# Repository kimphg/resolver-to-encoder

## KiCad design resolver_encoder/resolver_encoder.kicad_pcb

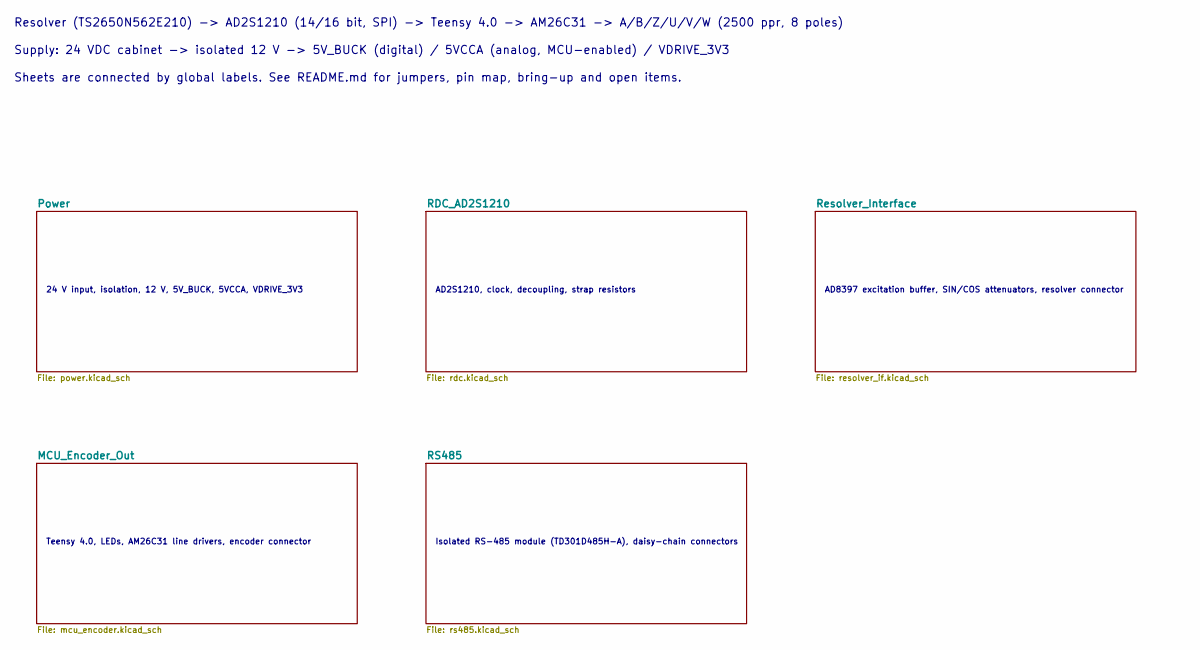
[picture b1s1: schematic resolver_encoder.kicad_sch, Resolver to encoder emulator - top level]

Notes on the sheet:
Resolver (TS2650N562E210) -> AD2S1210 (14/16 bit, SPI) -> Teensy 4.0 -> AM26C31 -> A/B/Z/U/V/W (2500 ppr, 8 poles)
Supply: 24 VDC cabinet -> isolated 12 V -> 5V_BUCK (digital) / 5VCCA (analog, MCU-enabled) / VDRIVE_3V3
Sheets are connected by global labels. See README.md for jumpers, pin map, bring-up and open items.
24 V input, isolation, 12 V, 5V_BUCK, 5VCCA, VDRIVE_3V3
AD2S1210, clock, decoupling, strap resistors
AD8397 excitation buffer, SIN/COS attenuators, resolver connector
Teensy 4.0, LEDs, AM26C31 line drivers, encoder connector
Isolated RS-485 module (TD301D485H-A), daisy-chain connectors

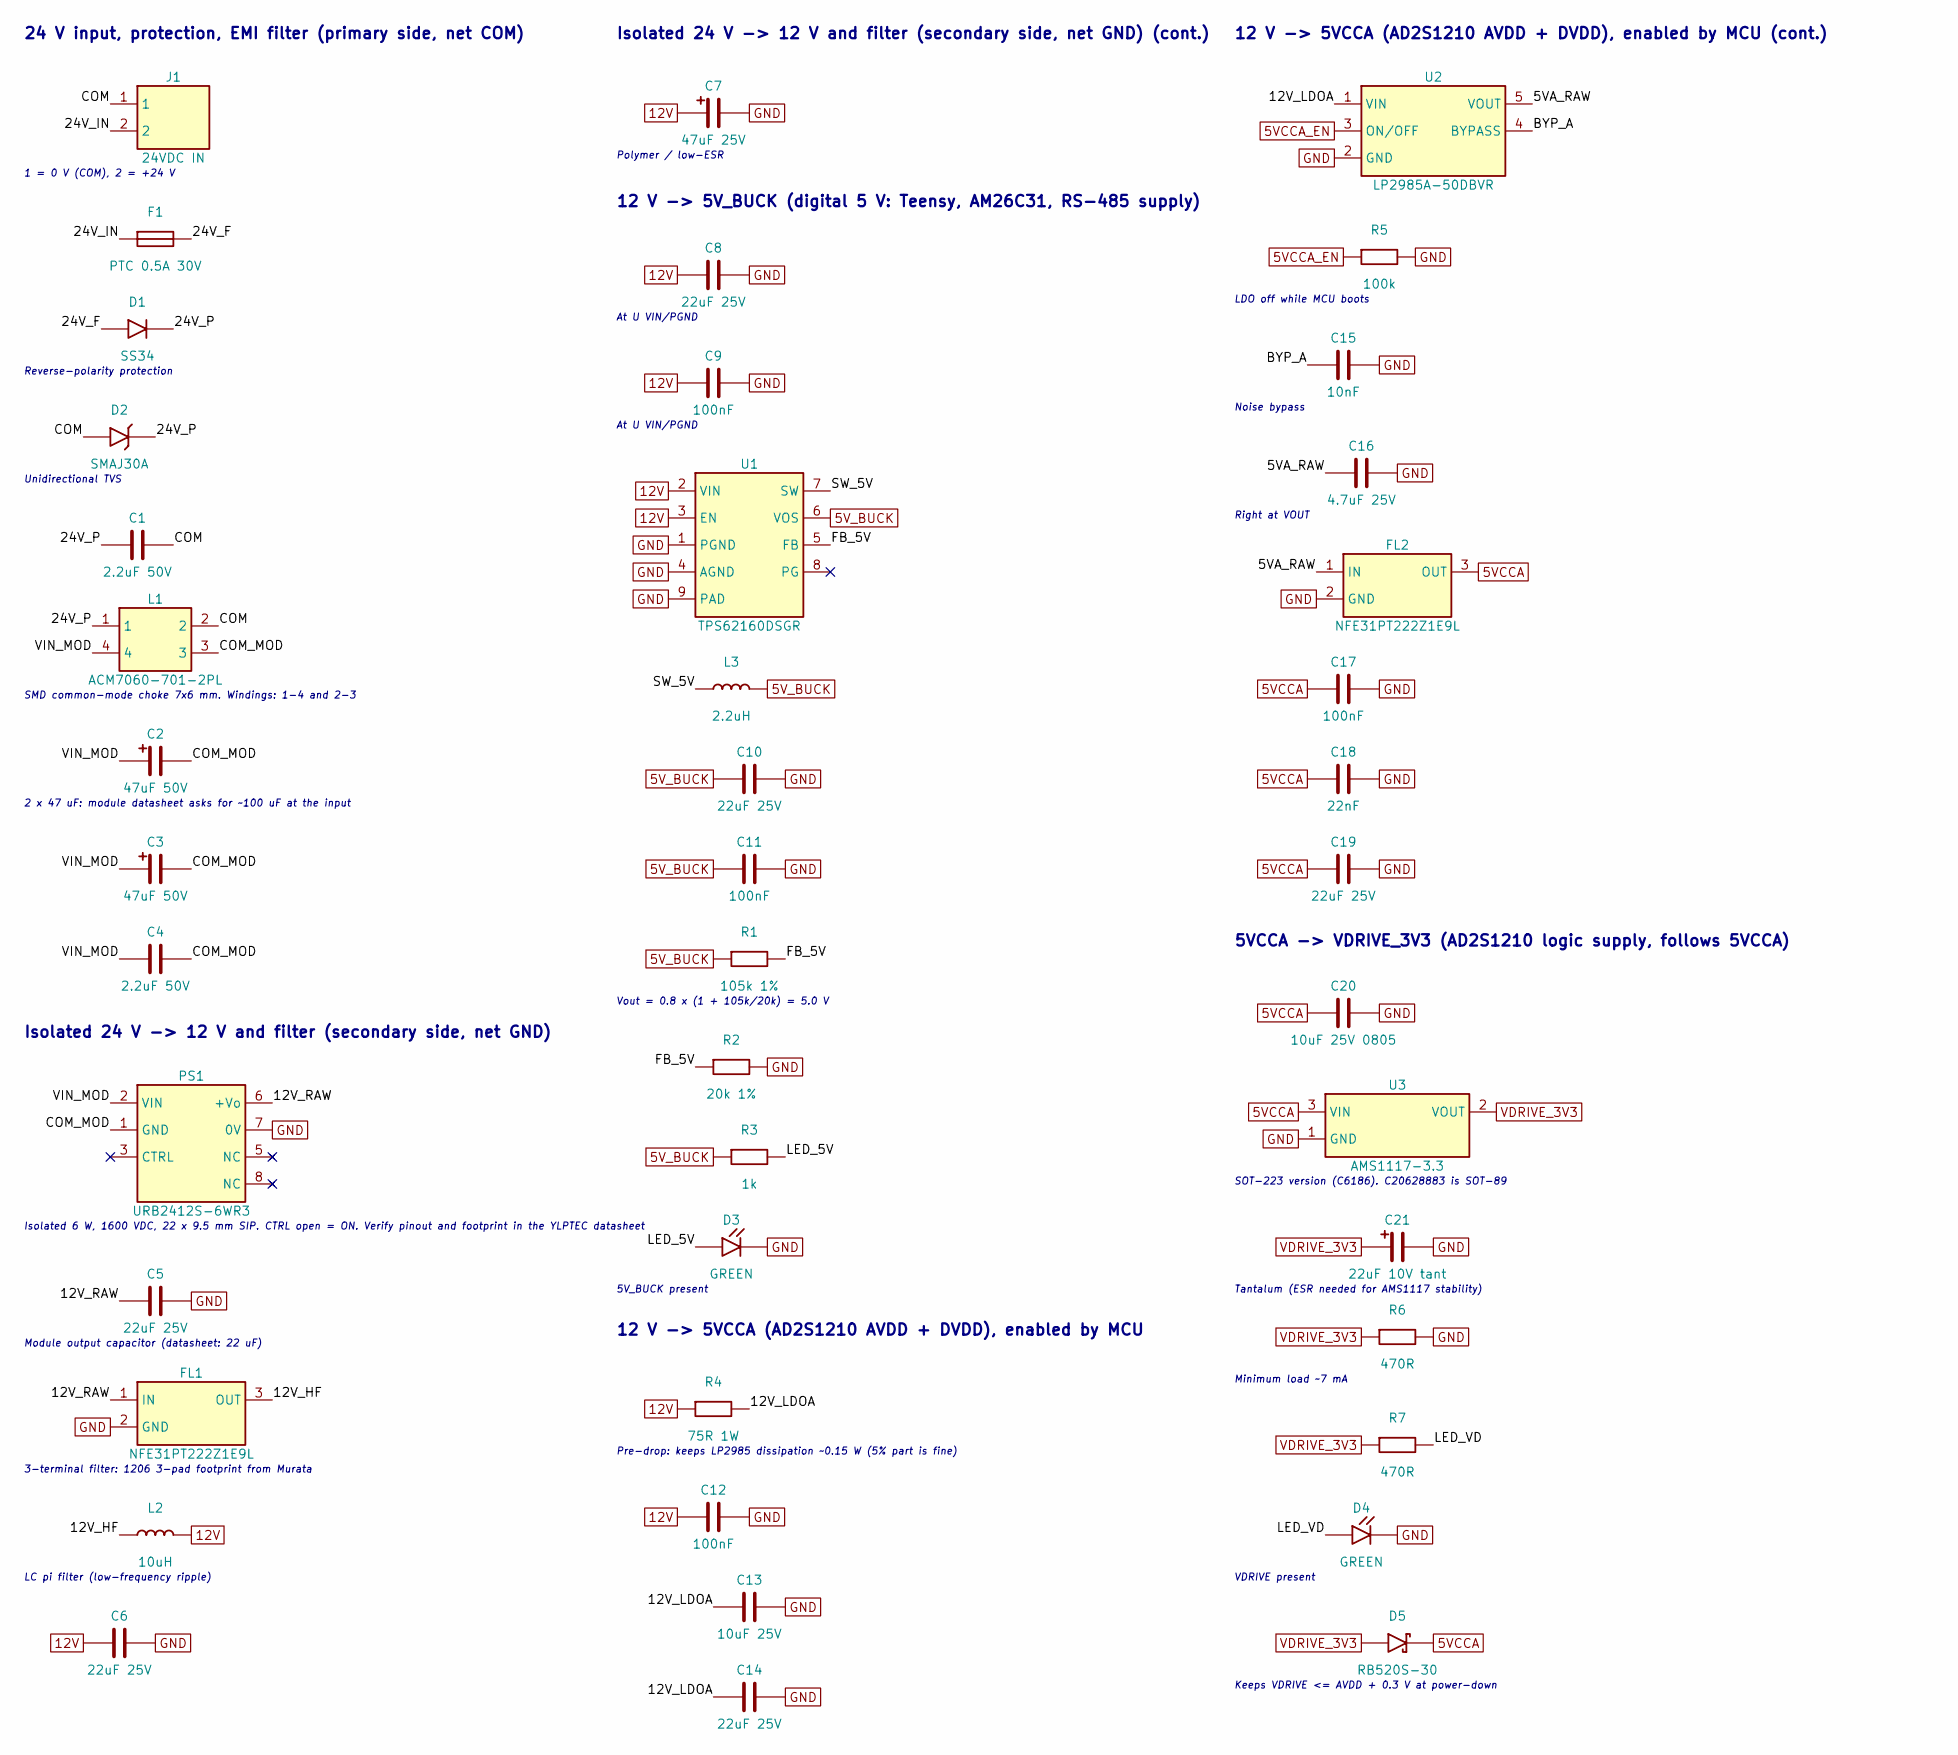
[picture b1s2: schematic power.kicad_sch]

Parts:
C1, C4: 2.2uF 50V; C_1206_3216Metric; MPN CL31B225KBHNNNE; LCSC C50254
C2, C3: 47uF 50V; CP_Elec_6.3x7.7; MPN RVT1H470M0607; LCSC C72523
C5, C6, C8, C10, C14, C19: 22uF 25V; C_1206_3216Metric; MPN CL31A226KAHNNNE; LCSC C12891
C7: 47uF 25V; CP_Elec_6.3x7.7; MPN 25SVPF47M; LCSC C136280
C9, C11, C12, C17: 100nF; C_0603_1608Metric; MPN CL10B104KB8NNNC; LCSC C1591
C13: 10uF 25V; C_1206_3216Metric; MPN CL31A106KAHNNNE; LCSC C9807
C15: 10nF; C_0603_1608Metric; MPN CL10B103KB8NNNC; LCSC C1589
C16: 4.7uF 25V; C_0805_2012Metric; MPN CL21A475KAQNNNE; LCSC C1779
C18: 22nF; C_0603_1608Metric; MPN CL10B223KB8NNNC; LCSC C21122
C20: 10uF 25V 0805; C_0805_2012Metric; MPN CL21A106KAYNNNE; LCSC C15850
C21: 22uF 10V tant; CP_EIA-3216-18_Kemet-A; MPN TAJA226K010RNJ; LCSC C11366
D1: SS34; D_SMA; MPN SS34; LCSC C8678
D2: SMAJ30A; D_SMA; MPN SMAJ30A; LCSC C353456
D3, D4: GREEN; LED_0805_2012Metric; MPN KT-0805G; LCSC C2297
D5: RB520S-30; D_SOD-523; MPN RB520S-30; LCSC C8522
F1: PTC 0.5A 30V; Fuse_1812_4532Metric; MPN SMD1812P050TF/30; LCSC C12559
FL1, FL2: NFE31PT222Z1E9L; Filter_Murata_NFE31PT_PROVISIONAL; MPN NFE31PT222Z1E9L; LCSC C86146
J1: 24VDC IN; PhoenixContact_MC_1,5_2-G-3.81_1x02_P3.81mm_Horizontal; MPN WJ15EDGRC-3.81-02P + plug WJ15EDGK-3.81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; LCSC C8387
L1: ACM7060-701-2PL; L_CommonModeChoke_TDK_ACM7060; MPN ACM7060-701-2PL-TL01; LCSC C78246
L2: 10uH; L_Bourns-SRN4018; MPN SRN4018-100M; LCSC C503307
L3: 2.2uH; L_Taiyo-Yuden_NR-40xx; MPN SMNR4020-2.2UH; LCSC C135262
PS1: URB2412S-6WR3; URB_S-6WR3_SIP8; MPN URB2412S-6WR3 (YLPTEC); LCSC C3031186
R1: 105k 1%; R_0603_1608Metric; MPN 0603WAF1053T5E; LCSC C16840
R2: 20k 1%; R_0603_1608Metric; MPN 0603WAF2002T5E; LCSC C4184
R3: 1k; R_0603_1608Metric; MPN 0603WAF1001T5E; LCSC C21190
R4: 75R 1W; R_2512_6332Metric; MPN 25121WJ0750T4E; LCSC C25493
R5: 100k; R_0603_1608Metric; MPN 0603WAF1003T5E; LCSC C25803
R6, R7: 470R; R_0603_1608Metric; MPN 0603WAF4700T5E; LCSC C23179
U1: TPS62160DSGR; WSON-8-1EP_2x2mm_P0.5mm_EP0.9x1.6mm; MPN TPS62160DSGR; LCSC C324077
U2: LP2985A-50DBVR; SOT-23-5; MPN LP2985A-50DBVR; LCSC C109382
U3: AMS1117-3.3; SOT-223-3_TabPin2; MPN AMS1117-3.3; LCSC C6186

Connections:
5VCCA: C17.1, C18.1, C19.1, C20.1, D5.1 (K), FL2.3 (OUT), U3.3 (VIN); also elsewhere on the board
5VCCA_EN: R5.1, U2.3 (ON/OFF); also elsewhere on the board
5V_BUCK: C10.1, C11.1, L3.2, R1.1, R3.1, U1.6 (VOS); also elsewhere on the board
12V: C6.1, C7.1, C8.1, C9.1, C12.1, L2.2, R4.1, U1.2 (VIN), U1.3 (EN); also elsewhere on the board
/Power/5VA_RAW: C16.1, FL2.1 (IN), U2.5 (VOUT)
/Power/12V_HF: FL1.3 (OUT), L2.1
/Power/12V_LDOA: C13.1, C14.1, R4.2, U2.1 (VIN)
/Power/12V_RAW: C5.1, FL1.1 (IN), PS1.6 (+Vo)
/Power/24V_F: D1.2 (A), F1.2
/Power/24V_IN: F1.1, J1.2
/Power/24V_P: C1.1, D1.1 (K), D2.1 (K), L1.1
/Power/BYP_A: C15.1, U2.4 (BYPASS)
/Power/COM: C1.2, D2.2 (A), J1.1, L1.2
/Power/COM_MOD: C2.2, C3.2, C4.2, L1.3, PS1.1 (GND)
/Power/FB_5V: R1.2, R2.1, U1.5 (FB)
/Power/LED_5V: D3.2 (A), R3.2
/Power/LED_VD: D4.2 (A), R7.2
/Power/SW_5V: L3.1, U1.7 (SW)
/Power/VIN_MOD: C2.1, C3.1, C4.1, L1.4, PS1.2 (VIN)
GND: C5.2, C6.2, C7.2, C8.2, C9.2, C10.2, C11.2, C12.2, C13.2, C14.2, C15.2, C16.2, C17.2, C18.2, C19.2, C20.2, C21.2, D3.1 (K), D4.1 (K), FL1.2 (GND), FL2.2 (GND), PS1.7 (0V), R2.2, R5.2, R6.2, U1.1 (PGND), U1.4 (AGND), U1.9 (PAD), U2.2 (GND), U3.1 (GND); also elsewhere on the board
VDRIVE_3V3: C21.1, D5.2 (A), R6.1, R7.1, U3.2 (VOUT); also elsewhere on the board

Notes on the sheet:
24 V input, protection, EMI filter (primary side, net COM)
1 = 0 V (COM), 2 = +24 V
Reverse-polarity protection
Unidirectional TVS
SMD common-mode choke 7x6 mm. Windings: 1-4 and 2-3
2 x 47 uF: module datasheet asks for ~100 uF at the input
Isolated 24 V -> 12 V and filter (secondary side, net GND)
Isolated 6 W, 1600 VDC, 22 x 9.5 mm SIP. CTRL open = ON. Verify pinout and footprint in the YLPTEC datasheet
Module output capacitor (datasheet: 22 uF)
3-terminal filter: 1206 3-pad footprint from Murata
LC pi filter (low-frequency ripple)
Isolated 24 V -> 12 V and filter (secondary side, net GND) (cont.)
Polymer / low-ESR
12 V -> 5V_BUCK (digital 5 V: Teensy, AM26C31, RS-485 supply)
At U VIN/PGND
Vout = 0.8 x (1 + 105k/20k) = 5.0 V
5V_BUCK present
12 V -> 5VCCA (AD2S1210 AVDD + DVDD), enabled by MCU
Pre-drop: keeps LP2985 dissipation ~0.15 W (5% part is fine)
12 V -> 5VCCA (AD2S1210 AVDD + DVDD), enabled by MCU (cont.)
LDO off while MCU boots
Noise bypass
Right at VOUT
5VCCA -> VDRIVE_3V3 (AD2S1210 logic supply, follows 5VCCA)
SOT-223 version (C6186). C20628883 is SOT-89
Tantalum (ESR needed for AMS1117 stability)
Minimum load ~7 mA
VDRIVE present
Keeps VDRIVE <= AVDD + 0.3 V at power-down

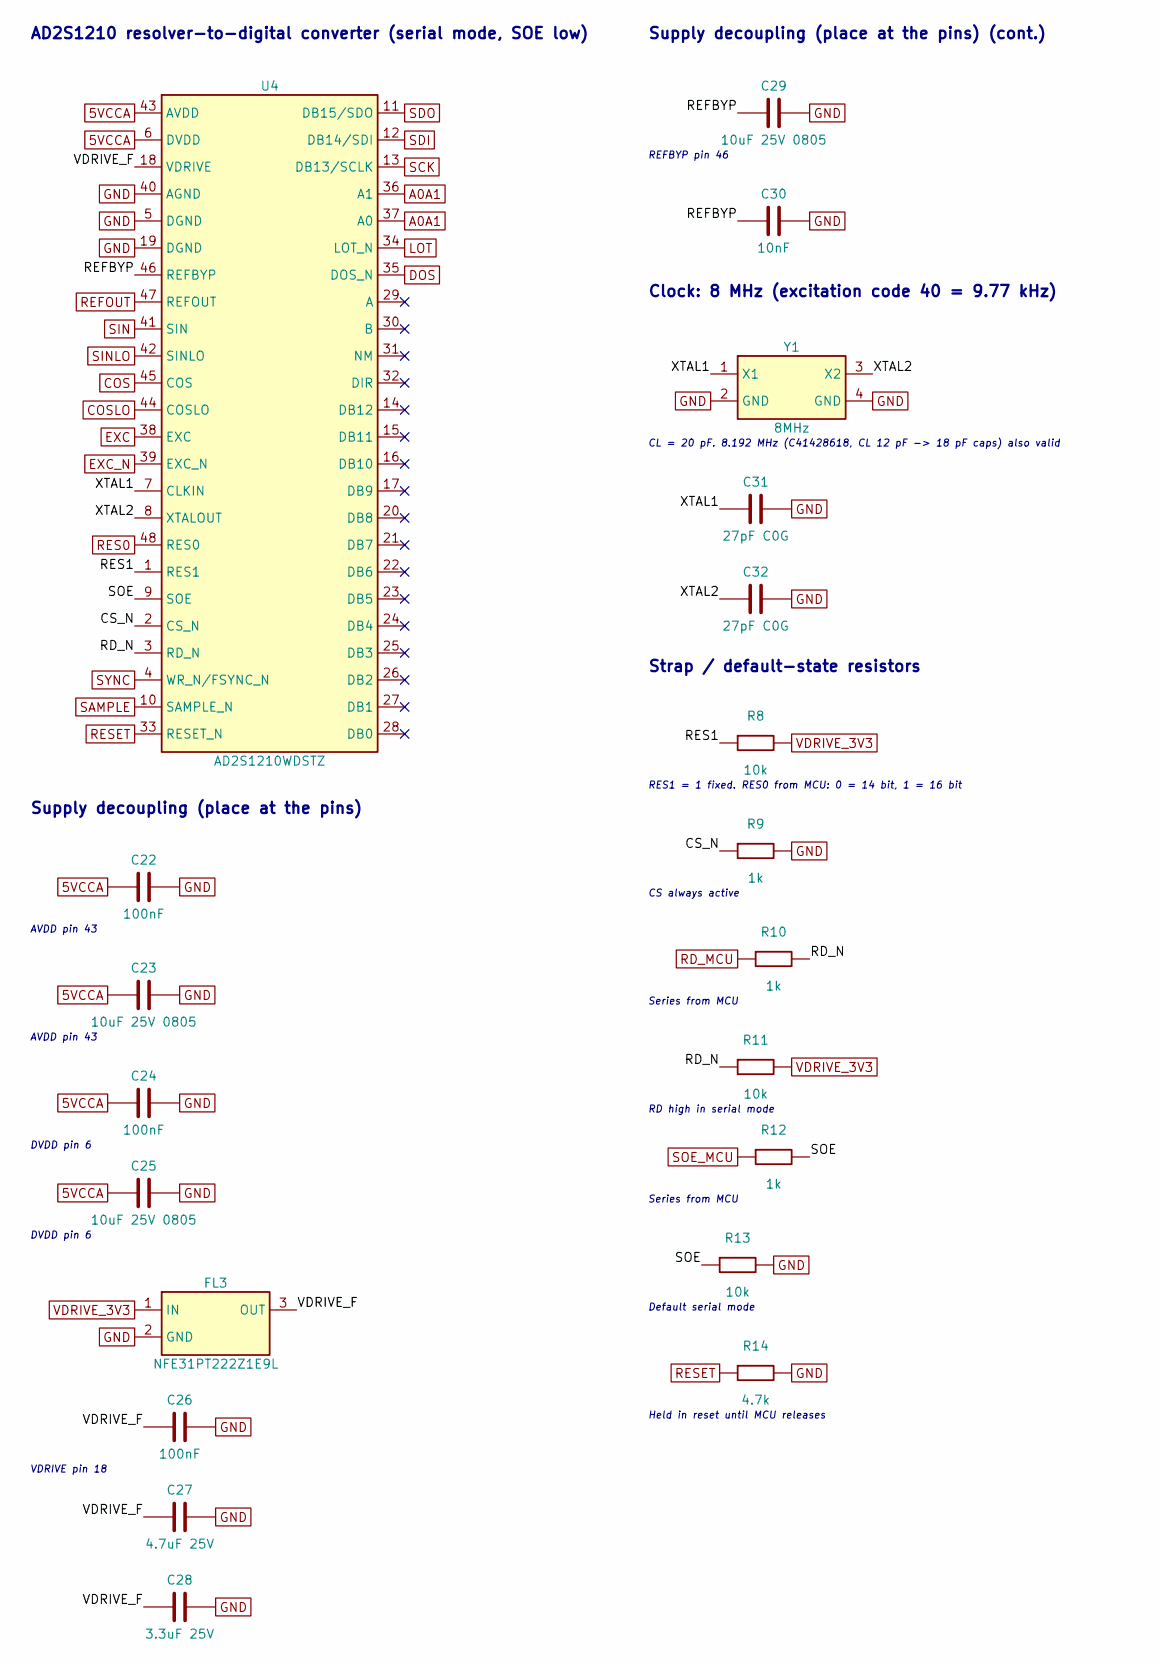
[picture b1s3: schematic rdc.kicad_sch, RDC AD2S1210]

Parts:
C22, C24, C26: 100nF; C_0603_1608Metric; MPN CL10B104KB8NNNC; LCSC C1591
C23, C25, C29: 10uF 25V 0805; C_0805_2012Metric; MPN CL21A106KAYNNNE; LCSC C15850
C27: 4.7uF 25V; C_0805_2012Metric; MPN CL21A475KAQNNNE; LCSC C1779
C28: 3.3uF 25V; C_0805_2012Metric; MPN TCC0805X7R335K250FT; LCSC C7393948
C30: 10nF; C_0603_1608Metric; MPN CL10B103KB8NNNC; LCSC C1589
C31, C32: 27pF C0G; C_0603_1608Metric; MPN CL10C270JB8NNNC; LCSC C1656
FL3: NFE31PT222Z1E9L; Filter_Murata_NFE31PT_PROVISIONAL; MPN NFE31PT222Z1E9L; LCSC C86146
R8, R11, R13: 10k; R_0603_1608Metric; MPN 0603WAF1002T5E; LCSC C25804
R9, R10, R12: 1k; R_0603_1608Metric; MPN 0603WAF1001T5E; LCSC C21190
R14: 4.7k; R_0603_1608Metric; MPN 0603WAF4701T5E; LCSC C23162
U4: AD2S1210WDSTZ; LQFP-48_7x7mm_P0.5mm; MPN AD2S1210WDSTZ; LCSC C443870
Y1: 8MHz; Crystal_SMD_3225-4Pin_3.2x2.5mm; MPN X32258MSB4SI; LCSC C2682774

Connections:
5VCCA: C22.1, C23.1, C24.1, C25.1, U4.6 (DVDD), U4.43 (AVDD); also elsewhere on the board
/RDC_AD2S1210/CS_N: R9.1, U4.2 (CS_N)
/RDC_AD2S1210/RD_N: R10.2, R11.1, U4.3 (RD_N)
/RDC_AD2S1210/REFBYP: C29.1, C30.1, U4.46 (REFBYP)
/RDC_AD2S1210/RES1: R8.1, U4.1 (RES1)
/RDC_AD2S1210/SOE: R12.2, R13.1, U4.9 (SOE)
/RDC_AD2S1210/VDRIVE_F: C26.1, C27.1, C28.1, FL3.3 (OUT), U4.18 (VDRIVE)
/RDC_AD2S1210/XTAL1: C31.1, U4.7 (CLKIN), Y1.1 (X1)
/RDC_AD2S1210/XTAL2: C32.1, U4.8 (XTALOUT), Y1.3 (X2)
A0A1: U4.36 (A1), U4.37 (A0); also elsewhere on the board
COS: U4.45 (COS); also elsewhere on the board
COSLO: U4.44 (COSLO); also elsewhere on the board
DOS: U4.35 (DOS_N); also elsewhere on the board
EXC: U4.38 (EXC); also elsewhere on the board
EXC_N: U4.39 (EXC_N); also elsewhere on the board
GND: C22.2, C23.2, C24.2, C25.2, C26.2, C27.2, C28.2, C29.2, C30.2, C31.2, C32.2, FL3.2 (GND), R9.2, R13.2, R14.2, U4.5 (DGND), U4.19 (DGND), U4.40 (AGND), Y1.2 (GND), Y1.4 (GND); also elsewhere on the board
LOT: U4.34 (LOT_N); also elsewhere on the board
RD_MCU: R10.1; also elsewhere on the board
REFOUT: U4.47 (REFOUT); also elsewhere on the board
RES0: U4.48 (RES0); also elsewhere on the board
RESET: R14.1, U4.33 (RESET_N); also elsewhere on the board
SAMPLE: U4.10 (SAMPLE_N); also elsewhere on the board
SCK: U4.13 (DB13/SCLK); also elsewhere on the board
SDI: U4.12 (DB14/SDI); also elsewhere on the board
SDO: U4.11 (DB15/SDO); also elsewhere on the board
SIN: U4.41 (SIN); also elsewhere on the board
SINLO: U4.42 (SINLO); also elsewhere on the board
SOE_MCU: R12.1; also elsewhere on the board
SYNC: U4.4 (WR_N/FSYNC_N); also elsewhere on the board
VDRIVE_3V3: FL3.1 (IN), R8.2, R11.2; also elsewhere on the board

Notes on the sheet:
AD2S1210 resolver-to-digital converter (serial mode, SOE low)
Supply decoupling (place at the pins)
AVDD pin 43
DVDD pin 6
VDRIVE pin 18
Supply decoupling (place at the pins) (cont.)
REFBYP pin 46
Clock: 8 MHz (excitation code 40 = 9.77 kHz)
CL = 20 pF. 8.192 MHz (C41428618, CL 12 pF -> 18 pF caps) also valid
Strap / default-state resistors
RES1 = 1 fixed. RES0 from MCU: 0 = 14 bit, 1 = 16 bit
CS always active
Series from MCU
RD high in serial mode
Default serial mode
Held in reset until MCU releases

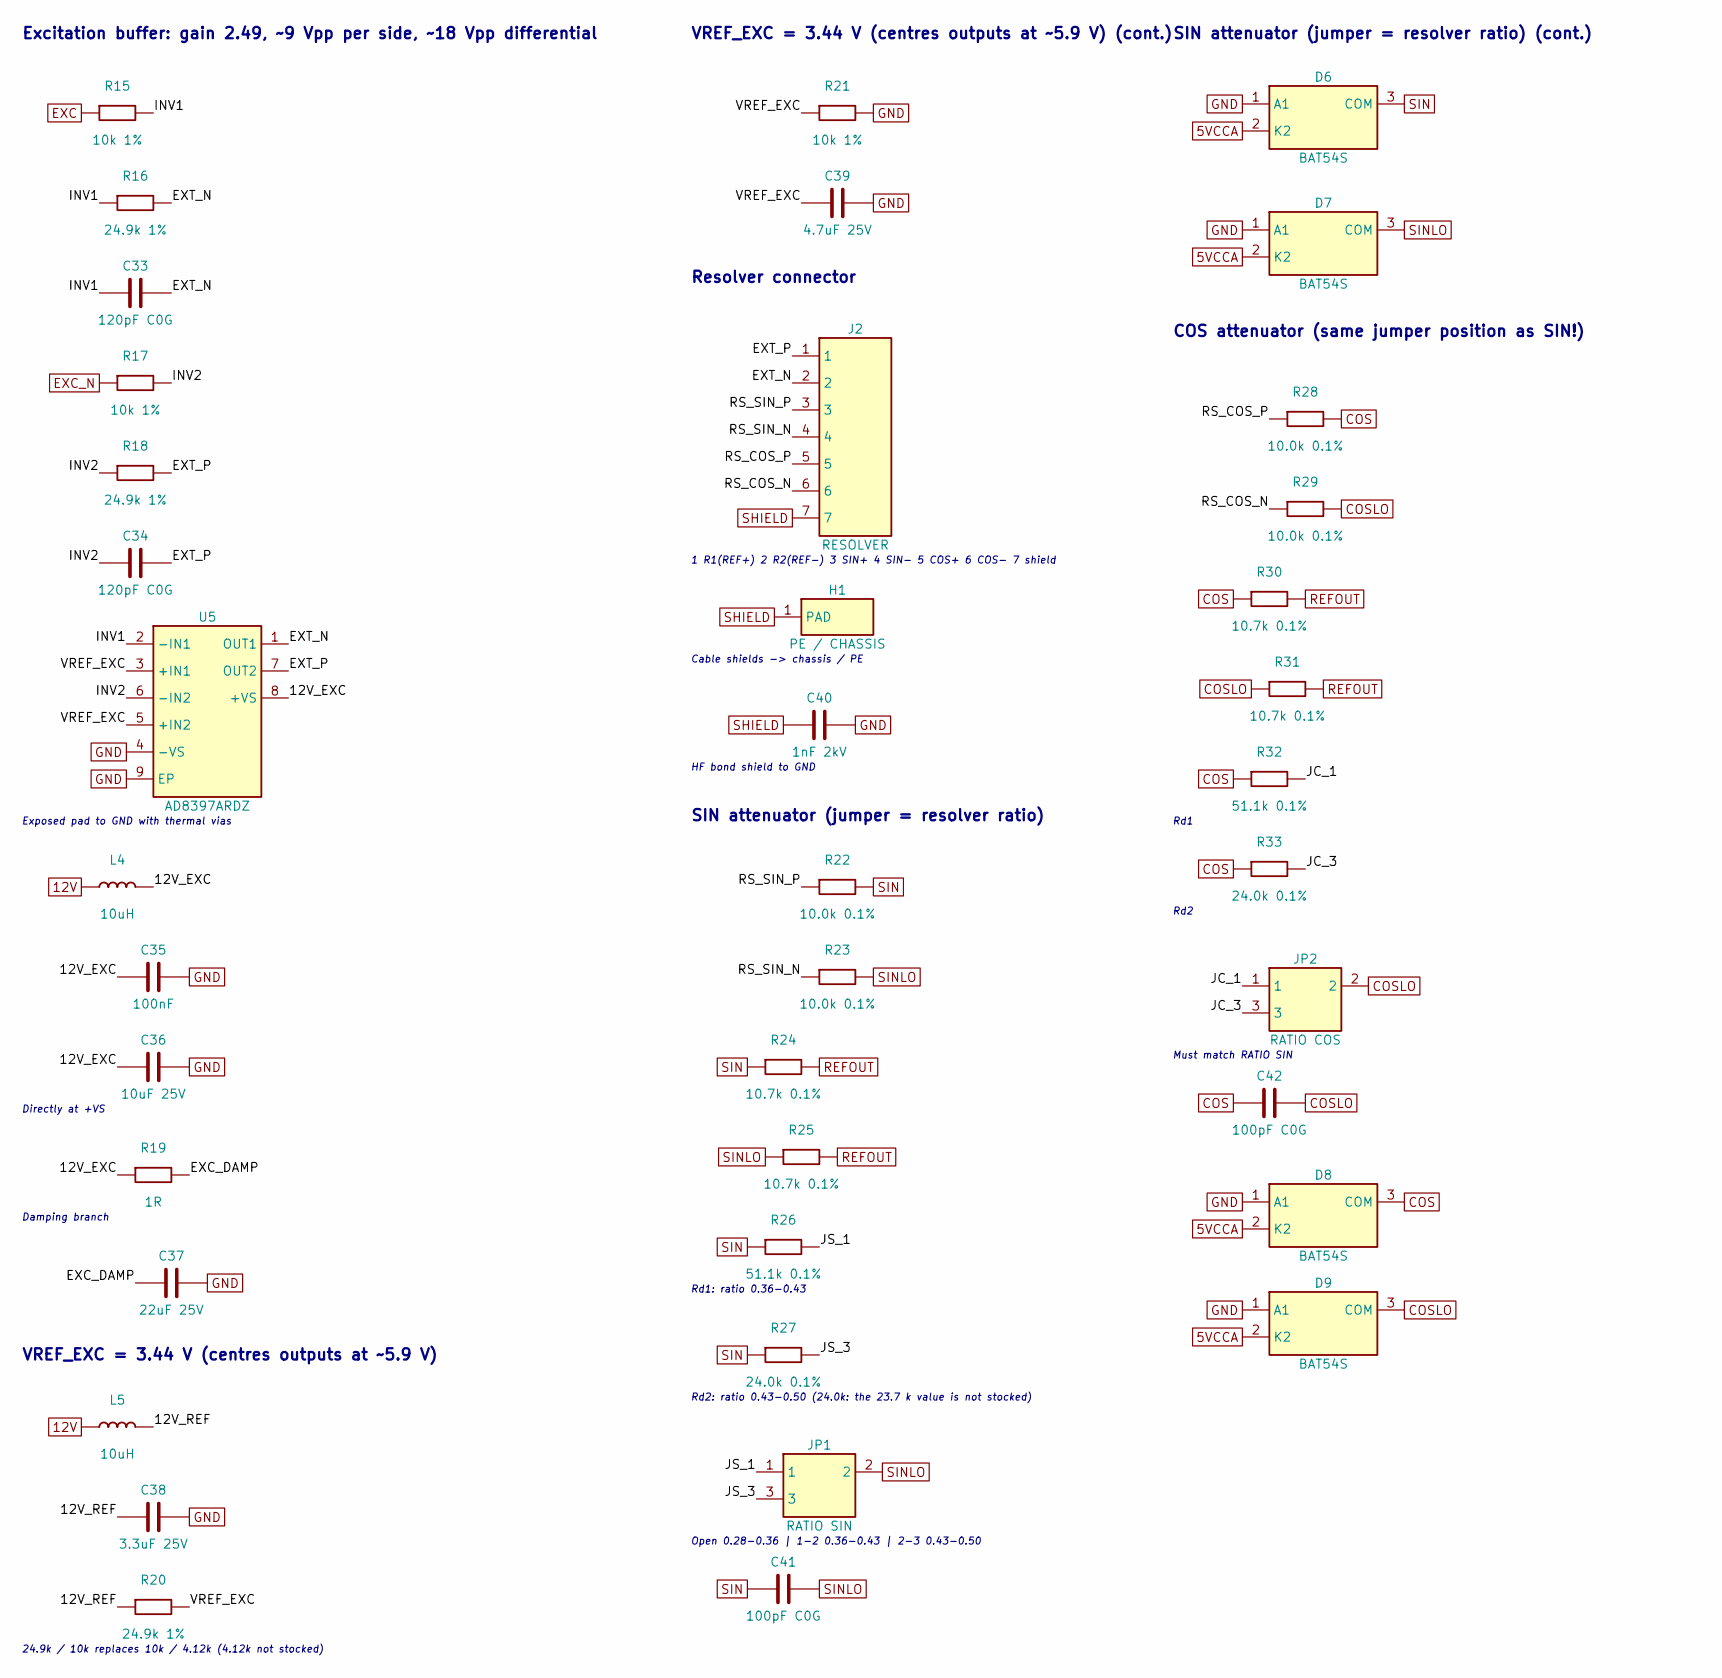
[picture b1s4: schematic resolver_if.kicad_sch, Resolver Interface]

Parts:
C33, C34: 120pF C0G; C_0603_1608Metric; MPN CL10C121JB8NNNC; LCSC C18438
C35: 100nF; C_0603_1608Metric; MPN CL10B104KB8NNNC; LCSC C1591
C36: 10uF 25V; C_1206_3216Metric; MPN CL31A106KAHNNNE; LCSC C9807
C37: 22uF 25V; C_1206_3216Metric; MPN CL31A226KAHNNNE; LCSC C12891
C38: 3.3uF 25V; C_0805_2012Metric; MPN TCC0805X7R335K250FT; LCSC C7393948
C39: 4.7uF 25V; C_0805_2012Metric; MPN CL21A475KAQNNNE; LCSC C1779
C40: 1nF 2kV; C_1206_3216Metric; MPN CC1206KKX7RDBB102; LCSC C23631
C41, C42: 100pF C0G; C_0603_1608Metric; MPN CL10C101JB8NNNC; LCSC C14858
D6, D7, D8, D9: BAT54S; SOT-23; MPN BAT54S; LCSC C916425
H1: PE / CHASSIS; MountingHole_3.2mm_M3_Pad5.0; MPN M3 mounting hole with pad
J2: RESOLVER; PhoenixContact_MC_1,5_7-G-3.81_1x07_P3.81mm_Horizontal; MPN WJ15EDGRC-3.81-07P + plug WJ15EDGK-3.81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; LCSC C24525
JP1: RATIO SIN; PinHeader_1x03_P2.54mm_Vertical; MPN 2.54 mm 1x40 header (cut) + jumper cap; LCSC C2337
JP2: RATIO COS; PinHeader_1x03_P2.54mm_Vertical; MPN 2.54 mm 1x40 header (cut) + jumper cap; LCSC C2337
L4, L5: 10uH; L_Bourns-SRN4018; MPN SRN4018-100M; LCSC C503307
R15, R17, R21: 10k 1%; R_0603_1608Metric; MPN 0603WAF1002T5E; LCSC C25804
R16, R18, R20: 24.9k 1%; R_0603_1608Metric; MPN 0603WAF2492T5E; LCSC C25962
R19: 1R; R_0603_1608Metric; MPN 0603WAF100KT5E; LCSC C22936
R22, R23, R28, R29: 10.0k 0.1%; R_0603_1608Metric; MPN RT0603BRD0710KL; LCSC C95204
R24, R25, R30, R31: 10.7k 0.1%; R_0603_1608Metric; MPN ERA-3AEB1072V; LCSC C2076333
R26, R32: 51.1k 0.1%; R_0603_1608Metric; MPN ERA3AEB5112V; LCSC C491138
R27, R33: 24.0k 0.1%; R_0603_1608Metric; MPN RT0603BRD0724KL; LCSC C326729
U5: AD8397ARDZ; SOIC-8-1EP_3.9x4.9mm_P1.27mm_EP2.29x3mm; MPN AD8397ARDZ; LCSC C578714

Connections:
5VCCA: D6.2 (K2), D7.2 (K2), D8.2 (K2), D9.2 (K2); also elsewhere on the board
12V: L4.1, L5.1; also elsewhere on the board
/Resolver_Interface/12V_EXC: C35.1, C36.1, L4.2, R19.1, U5.8 (+VS)
/Resolver_Interface/12V_REF: C38.1, L5.2, R20.1
/Resolver_Interface/EXC_DAMP: C37.1, R19.2
/Resolver_Interface/EXT_N: C33.2, J2.2, R16.2, U5.1 (OUT1)
/Resolver_Interface/EXT_P: C34.2, J2.1, R18.2, U5.7 (OUT2)
/Resolver_Interface/INV1: C33.1, R15.2, R16.1, U5.2 (-IN1)
/Resolver_Interface/INV2: C34.1, R17.2, R18.1, U5.6 (-IN2)
/Resolver_Interface/JC_1: JP2.1, R32.2
/Resolver_Interface/JC_3: JP2.3, R33.2
/Resolver_Interface/JS_1: JP1.1, R26.2
/Resolver_Interface/JS_3: JP1.3, R27.2
/Resolver_Interface/RS_COS_N: J2.6, R29.1
/Resolver_Interface/RS_COS_P: J2.5, R28.1
/Resolver_Interface/RS_SIN_N: J2.4, R23.1
/Resolver_Interface/RS_SIN_P: J2.3, R22.1
/Resolver_Interface/VREF_EXC: C39.1, R20.2, R21.1, U5.3 (+IN1), U5.5 (+IN2)
COS: C42.1, D8.3 (COM), R28.2, R30.1, R32.1, R33.1; also elsewhere on the board
COSLO: C42.2, D9.3 (COM), JP2.2, R29.2, R31.1; also elsewhere on the board
EXC: R15.1; also elsewhere on the board
EXC_N: R17.1; also elsewhere on the board
GND: C35.2, C36.2, C37.2, C38.2, C39.2, C40.2, D6.1 (A1), D7.1 (A1), D8.1 (A1), D9.1 (A1), R21.2, U5.4 (-VS), U5.9 (EP); also elsewhere on the board
REFOUT: R24.2, R25.2, R30.2, R31.2; also elsewhere on the board
SHIELD: C40.1, H1.1, J2.7; also elsewhere on the board
SIN: C41.1, D6.3 (COM), R22.2, R24.1, R26.1, R27.1; also elsewhere on the board
SINLO: C41.2, D7.3 (COM), JP1.2, R23.2, R25.1; also elsewhere on the board

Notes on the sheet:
Excitation buffer: gain 2.49, ~9 Vpp per side, ~18 Vpp differential
Exposed pad to GND with thermal vias
Directly at +VS
Damping branch
VREF_EXC = 3.44 V (centres outputs at ~5.9 V)
24.9k / 10k replaces 10k / 4.12k (4.12k not stocked)
VREF_EXC = 3.44 V (centres outputs at ~5.9 V) (cont.)
Resolver connector
1 R1(REF+) 2 R2(REF-) 3 SIN+ 4 SIN- 5 COS+ 6 COS- 7 shield
Cable shields -> chassis / PE
HF bond shield to GND
SIN attenuator (jumper = resolver ratio)
Rd1: ratio 0.36-0.43
Rd2: ratio 0.43-0.50 (24.0k: the 23.7 k value is not stocked)
Open 0.28-0.36 | 1-2 0.36-0.43 | 2-3 0.43-0.50
SIN attenuator (jumper = resolver ratio) (cont.)
COS attenuator (same jumper position as SIN!)
Rd1
Rd2
Must match RATIO SIN

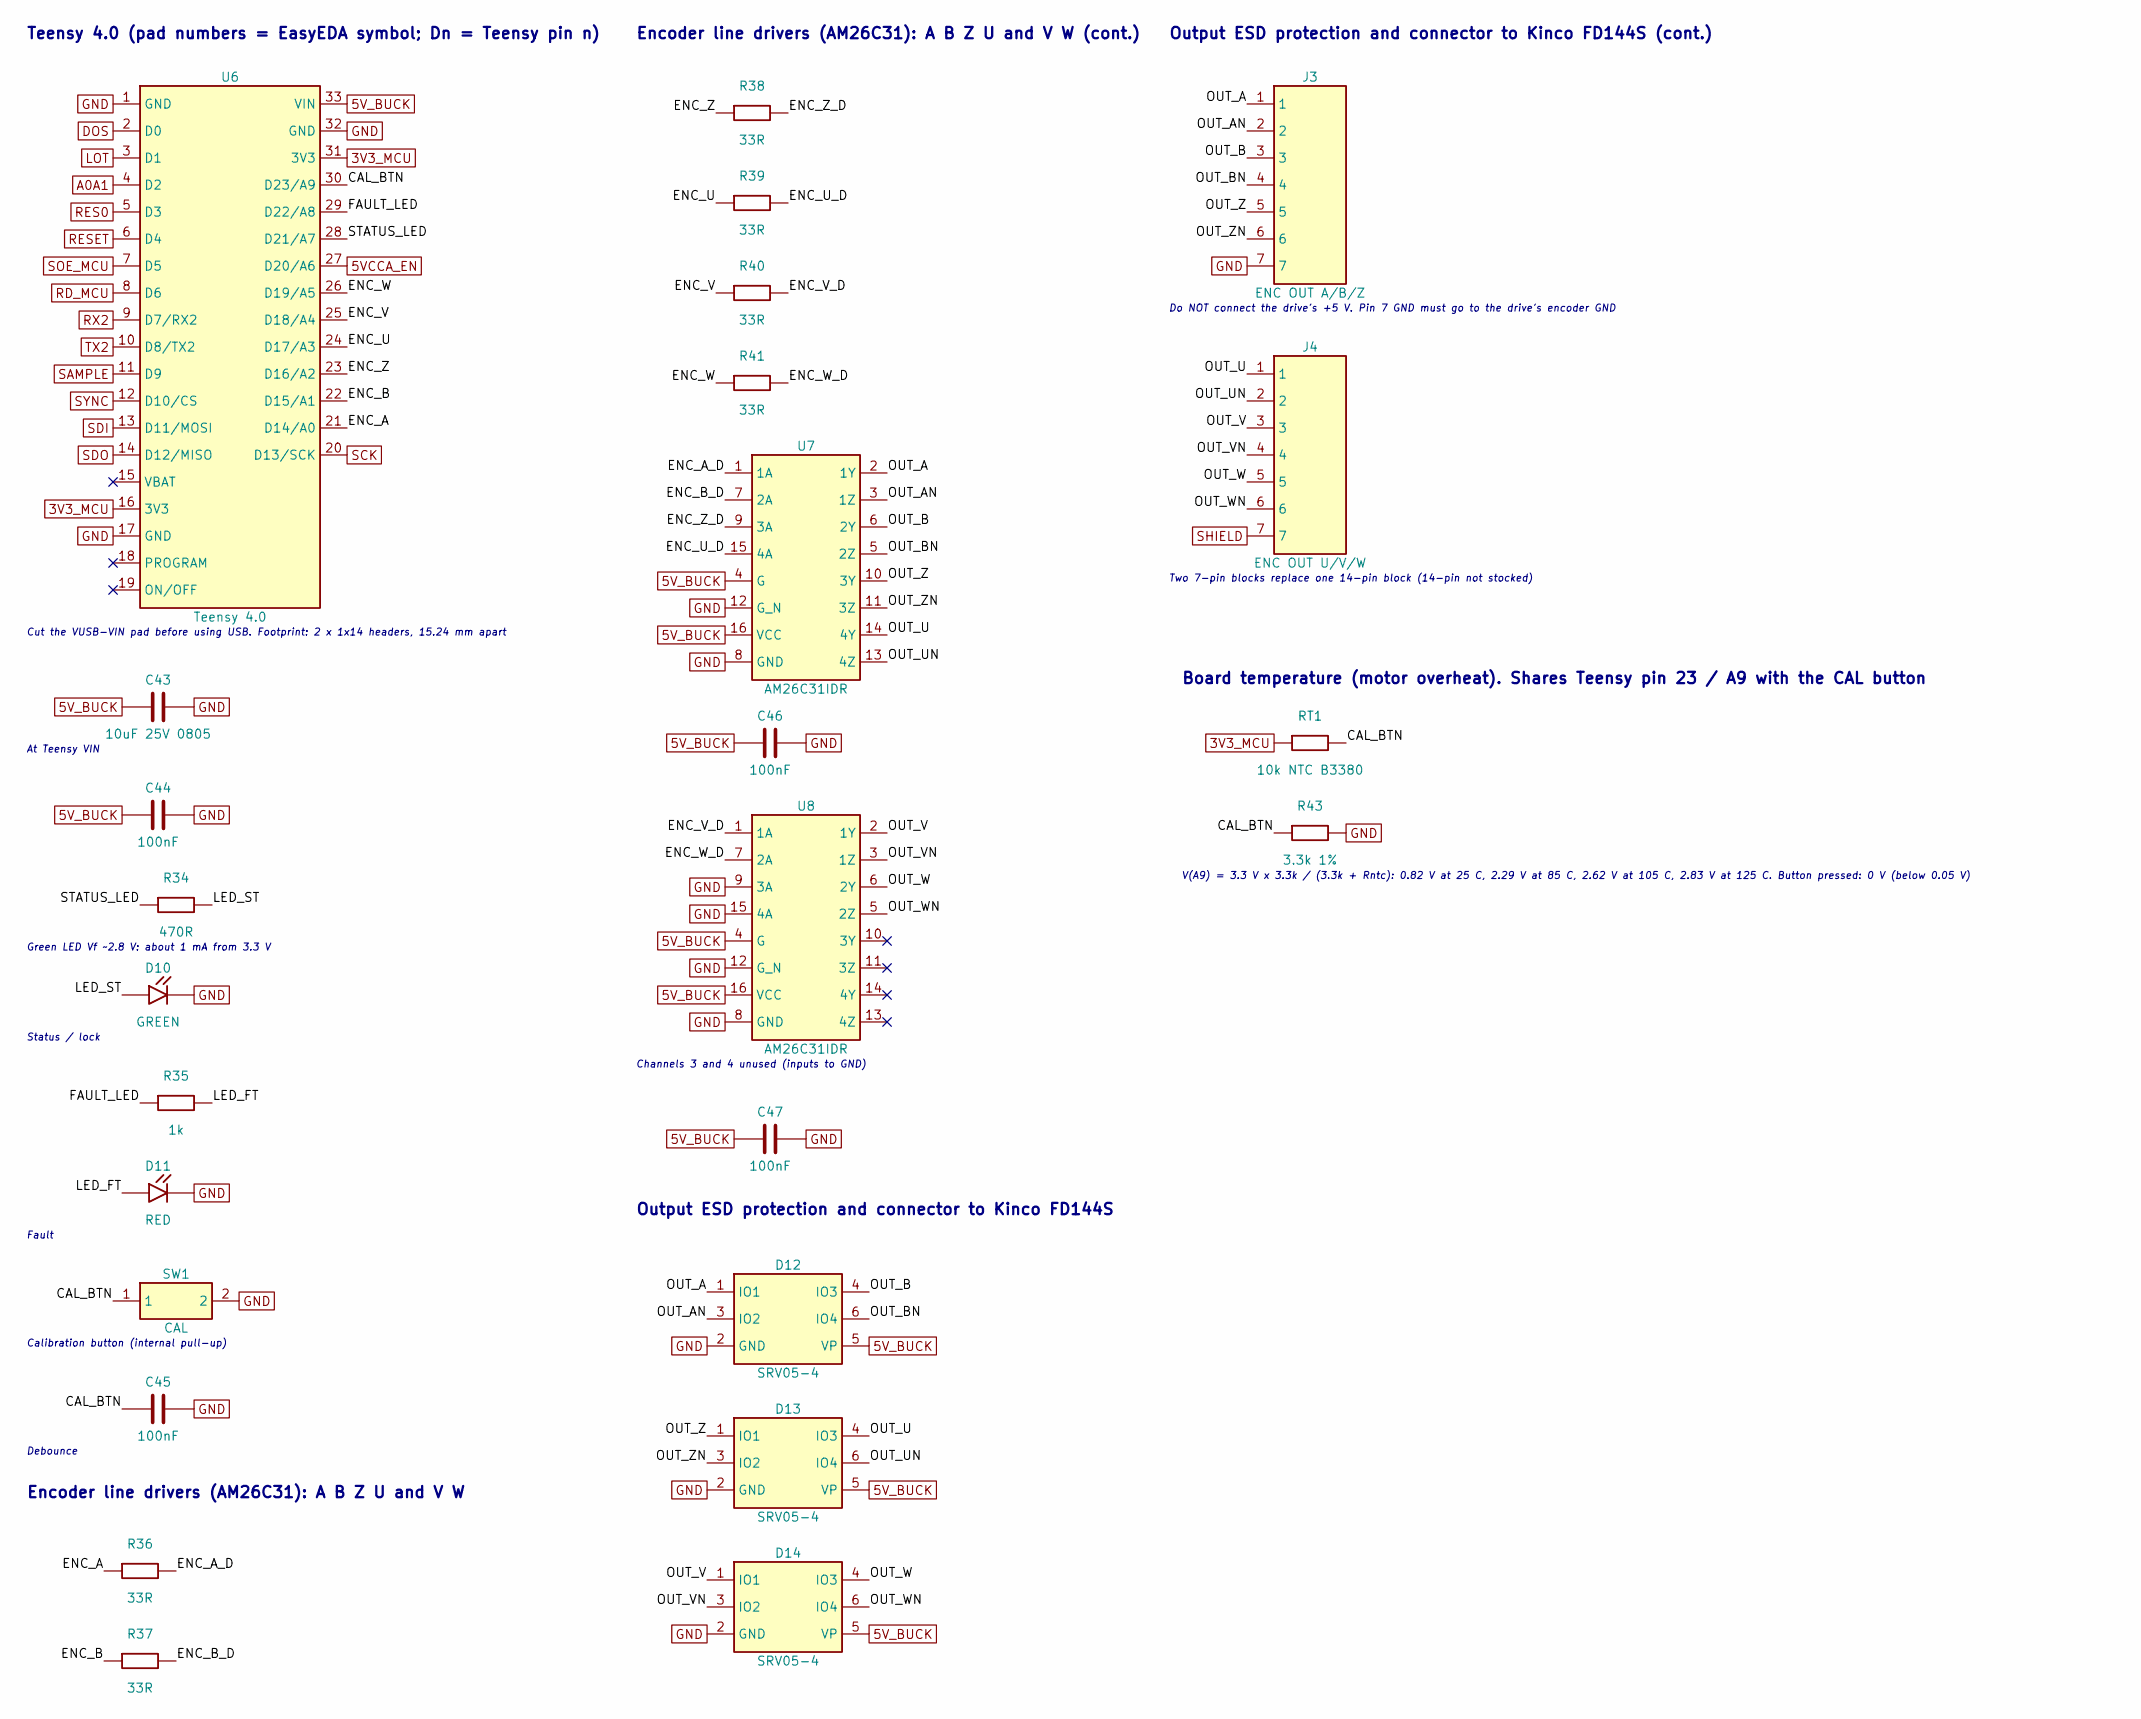
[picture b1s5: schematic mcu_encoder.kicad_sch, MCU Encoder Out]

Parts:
C43: 10uF 25V 0805; C_0805_2012Metric; MPN CL21A106KAYNNNE; LCSC C15850
C44, C45, C46, C47: 100nF; C_0603_1608Metric; MPN CL10B104KB8NNNC; LCSC C1591
D10: GREEN; LED_0805_2012Metric; MPN KT-0805G; LCSC C2297
D11: RED; LED_0805_2012Metric; MPN NCD0805R1; LCSC C84256
D12, D13, D14: SRV05-4; SOT-23-6; MPN SRV05-4; LCSC C558418
J3: ENC OUT A/B/Z; PhoenixContact_MC_1,5_7-G-3.81_1x07_P3.81mm_Horizontal; MPN WJ15EDGRC-3.81-07P + plug WJ15EDGK-3.81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; LCSC C24525
J4: ENC OUT U/V/W; PhoenixContact_MC_1,5_7-G-3.81_1x07_P3.81mm_Horizontal; MPN WJ15EDGRC-3.81-07P + plug WJ15EDGK-3.81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; LCSC C24525
R34: 470R; R_0603_1608Metric; MPN 0603WAF4700T5E; LCSC C23179
R35: 1k; R_0603_1608Metric; MPN 0603WAF1001T5E; LCSC C21190
R36, R37, R38, R39, R40, R41: 33R; R_0603_1608Metric; MPN 0603WAF330JT5E; LCSC C23140
R43: 3.3k 1%; R_0603_1608Metric; MPN 0603WAF3301T5E; LCSC C22978
RT1: 10k NTC B3380; R_0603_1608Metric; MPN NCP18XH103F03RB; LCSC C13564
SW1: CAL; SW_Push_1P1T_NO_E-Switch_TL3301NxxxxxG; MPN TS-1102S-B-G-B; LCSC C381064
U6: Teensy 4.0; Teensy40_Sockets_2x14; MPN PJRC Teensy 4.0 (not on LCSC); sockets: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; LCSC C2905420
U7, U8: AM26C31IDR; SOIC-16_3.9x9.9mm_P1.27mm; MPN AM26C31IDR; LCSC C34923

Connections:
3V3_MCU: RT1.1, U6.16 (3V3), U6.31 (3V3); also elsewhere on the board
5VCCA_EN: U6.27 (D20/A6); also elsewhere on the board
5V_BUCK: C43.1, C44.1, C46.1, C47.1, D12.5 (VP), D13.5 (VP), D14.5 (VP), U6.33 (VIN), U7.4 (G), U7.16 (VCC), U8.4 (G), U8.16 (VCC); also elsewhere on the board
/MCU_Encoder_Out/CAL_BTN: C45.1, R43.1, RT1.2, SW1.1, U6.30 (D23/A9)
/MCU_Encoder_Out/ENC_A: R36.1, U6.21 (D14/A0)
/MCU_Encoder_Out/ENC_A_D: R36.2, U7.1 (1A)
/MCU_Encoder_Out/ENC_B: R37.1, U6.22 (D15/A1)
/MCU_Encoder_Out/ENC_B_D: R37.2, U7.7 (2A)
/MCU_Encoder_Out/ENC_U: R39.1, U6.24 (D17/A3)
/MCU_Encoder_Out/ENC_U_D: R39.2, U7.15 (4A)
/MCU_Encoder_Out/ENC_V: R40.1, U6.25 (D18/A4)
/MCU_Encoder_Out/ENC_V_D: R40.2, U8.1 (1A)
/MCU_Encoder_Out/ENC_W: R41.1, U6.26 (D19/A5)
/MCU_Encoder_Out/ENC_W_D: R41.2, U8.7 (2A)
/MCU_Encoder_Out/ENC_Z: R38.1, U6.23 (D16/A2)
/MCU_Encoder_Out/ENC_Z_D: R38.2, U7.9 (3A)
/MCU_Encoder_Out/FAULT_LED: R35.1, U6.29 (D22/A8)
/MCU_Encoder_Out/LED_FT: D11.2 (A), R35.2
/MCU_Encoder_Out/LED_ST: D10.2 (A), R34.2
/MCU_Encoder_Out/OUT_A: D12.1 (IO1), J3.1, U7.2 (1Y)
/MCU_Encoder_Out/OUT_AN: D12.3 (IO2), J3.2, U7.3 (1Z)
/MCU_Encoder_Out/OUT_B: D12.4 (IO3), J3.3, U7.6 (2Y)
/MCU_Encoder_Out/OUT_BN: D12.6 (IO4), J3.4, U7.5 (2Z)
/MCU_Encoder_Out/OUT_U: D13.4 (IO3), J4.1, U7.14 (4Y)
/MCU_Encoder_Out/OUT_UN: D13.6 (IO4), J4.2, U7.13 (4Z)
/MCU_Encoder_Out/OUT_V: D14.1 (IO1), J4.3, U8.2 (1Y)
/MCU_Encoder_Out/OUT_VN: D14.3 (IO2), J4.4, U8.3 (1Z)
/MCU_Encoder_Out/OUT_W: D14.4 (IO3), J4.5, U8.6 (2Y)
/MCU_Encoder_Out/OUT_WN: D14.6 (IO4), J4.6, U8.5 (2Z)
/MCU_Encoder_Out/OUT_Z: D13.1 (IO1), J3.5, U7.10 (3Y)
/MCU_Encoder_Out/OUT_ZN: D13.3 (IO2), J3.6, U7.11 (3Z)
/MCU_Encoder_Out/STATUS_LED: R34.1, U6.28 (D21/A7)
A0A1: U6.4 (D2); also elsewhere on the board
DOS: U6.2 (D0); also elsewhere on the board
GND: C43.2, C44.2, C45.2, C46.2, C47.2, D10.1 (K), D11.1 (K), D12.2 (GND), D13.2 (GND), D14.2 (GND), J3.7, R43.2, SW1.2, U6.1 (GND), U6.17 (GND), U6.32 (GND), U7.8 (GND), U7.12 (G_N), U8.8 (GND), U8.9 (3A), U8.12 (G_N), U8.15 (4A); also elsewhere on the board
LOT: U6.3 (D1); also elsewhere on the board
RD_MCU: U6.8 (D6); also elsewhere on the board
RES0: U6.5 (D3); also elsewhere on the board
RESET: U6.6 (D4); also elsewhere on the board
RX2: U6.9 (D7/RX2); also elsewhere on the board
SAMPLE: U6.11 (D9); also elsewhere on the board
SCK: U6.20 (D13/SCK); also elsewhere on the board
SDI: U6.13 (D11/MOSI); also elsewhere on the board
SDO: U6.14 (D12/MISO); also elsewhere on the board
SHIELD: J4.7; also elsewhere on the board
SOE_MCU: U6.7 (D5); also elsewhere on the board
SYNC: U6.12 (D10/CS); also elsewhere on the board
TX2: U6.10 (D8/TX2); also elsewhere on the board

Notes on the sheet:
Teensy 4.0 (pad numbers = EasyEDA symbol; Dn = Teensy pin n)
Cut the VUSB-VIN pad before using USB. Footprint: 2 x 1x14 headers, 15.24 mm apart
At Teensy VIN
Green LED Vf ~2.8 V: about 1 mA from 3.3 V
Status / lock
Fault
Board temperature (motor overheat). Shares Teensy pin 23 / A9 with the CAL button
V(A9) = 3.3 V x 3.3k / (3.3k + Rntc): 0.82 V at 25 C, 2.29 V at 85 C, 2.62 V at 105 C, 2.83 V at 125 C. Button pressed: 0 V (below 0.05 V)
Calibration button (internal pull-up)
Debounce
Encoder line drivers (AM26C31): A B Z U and V W
Encoder line drivers (AM26C31): A B Z U and V W (cont.)
Channels 3 and 4 unused (inputs to GND)
Output ESD protection and connector to Kinco FD144S
Output ESD protection and connector to Kinco FD144S (cont.)
Do NOT connect the drive's +5 V. Pin 7 GND must go to the drive's encoder GND
Two 7-pin blocks replace one 14-pin block (14-pin not stocked)
